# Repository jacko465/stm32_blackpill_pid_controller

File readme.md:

# STM32 Black Pill PID Motor Controller

*v1 deployment of the PID controller. With Pololu 4035 driver modules*

A PID-based motor control system for the STM32F411 Black Pill microcontroller, designed to control 4 DC motors with encoders via H-bridge drivers (e.g., TI DRV8874).

## Features

- **High-frequency PID control**: 1 kHz PID loop running on TIM10 interrupt
- **Encoder feedback**: 100 Hz encoder updates (quadrature decoding)
- **4 independent motor channels**: Each with PWM speed control and direction control
- **Configurable PID gains**: Kp, Ki, Kd parameters per motor
- **Anti-windup protection**: Integral clamping to prevent windup

## Hardware Configuration

### Motor Specifications
- Encoder: 11 PPR (basic) × 4 (quadrature) × 35.5 (gear ratio) = **1562 counts/revolution**
- PWM Frequency: Configured via TIM1 = 20kHz
- Control Loop: 1 ms update period (1 kHz)
- Encoder Reading: 10 ms update period (100 Hz)

### System Clock
- **84 MHz SYSCLK** derived from 25 MHz HSE crystal
- Configured with PLL (PLLM=25, PLLN=336, PLLP=4)

## Pinout

| Function | Pin | Timer/Channel |
|----------|-----|---------------|
| **Motor 1 PWM** | PA8 | TIM1 CH1 |
| **Motor 2 PWM** | PA9 | TIM1 CH2 |
| **Motor 3 PWM** | PA10 | TIM1 CH3 |
| **Motor 4 PWM** | PA11 | TIM1 CH4 |
| **Motor 1 DIR** | PB0 | GPIO |
| **Motor 2 DIR** | PB1 | GPIO |
| **Motor 3 DIR** | PB2 | GPIO |
| **Motor 4 DIR** | PB10 | GPIO |
| **Motor 1 Encoder A** | PA0 | TIM5 CH1 |
| **Motor 1 Encoder B** | PA1 | TIM5 CH2 |
| **Motor 2 Encoder A** | PA6 | TIM3 CH1 |
| **Motor 2 Encoder B** | PA7 | TIM3 CH2 |
| **Motor 3 Encoder A** | PB6 | TIM4 CH1 |
| **Motor 3 Encoder B** | PB7 | TIM4 CH2 |
| **Motor 4 Encoder A** | PA5 | TIM2 CH1 |
| **Motor 4 Encoder B** | PB3 | TIM2 CH2 |
| **USART2 TX** | PA2 | USART2 |
| **USART2 RX** | PA3 | USART2 |
| **LED** | PC13 | GPIO (onboard) |

## PID Configuration

Default PID gains (defined in [`motor.h`](include/motor.h)):
- **Kp**: 0.1
- **Ki**: 0.125
- **Kd**: 0.0
- **Integral Limit**: 5.0 (anti-windup)
- **Output Range**: -1.0 to 1.0 (bidirectional control)

## Motor Control Functions

This project has been coded for EN/PH driver control mode

The [`motor.c`](src/motor.c) module provides:
- `Motor_SetTargetRPM()`: Set target velocity in RPM
- `Motor_Forward()`: Drive motor forward with duty cycle
- `Motor_Reverse()`: Drive motor in reverse with duty cycle
- `Motor_Break()`: Active braking (both H-bridge outputs high)
- `Motor_Coast()`: Free-running coast (both outputs low)

## Building

This project uses **PlatformIO**. To build and upload

## Error Handling

The [`Error_Handler()`](src/main.c) function provides visual feedback via fast blinking of the onboard LED (PC13) if system initialization fails.

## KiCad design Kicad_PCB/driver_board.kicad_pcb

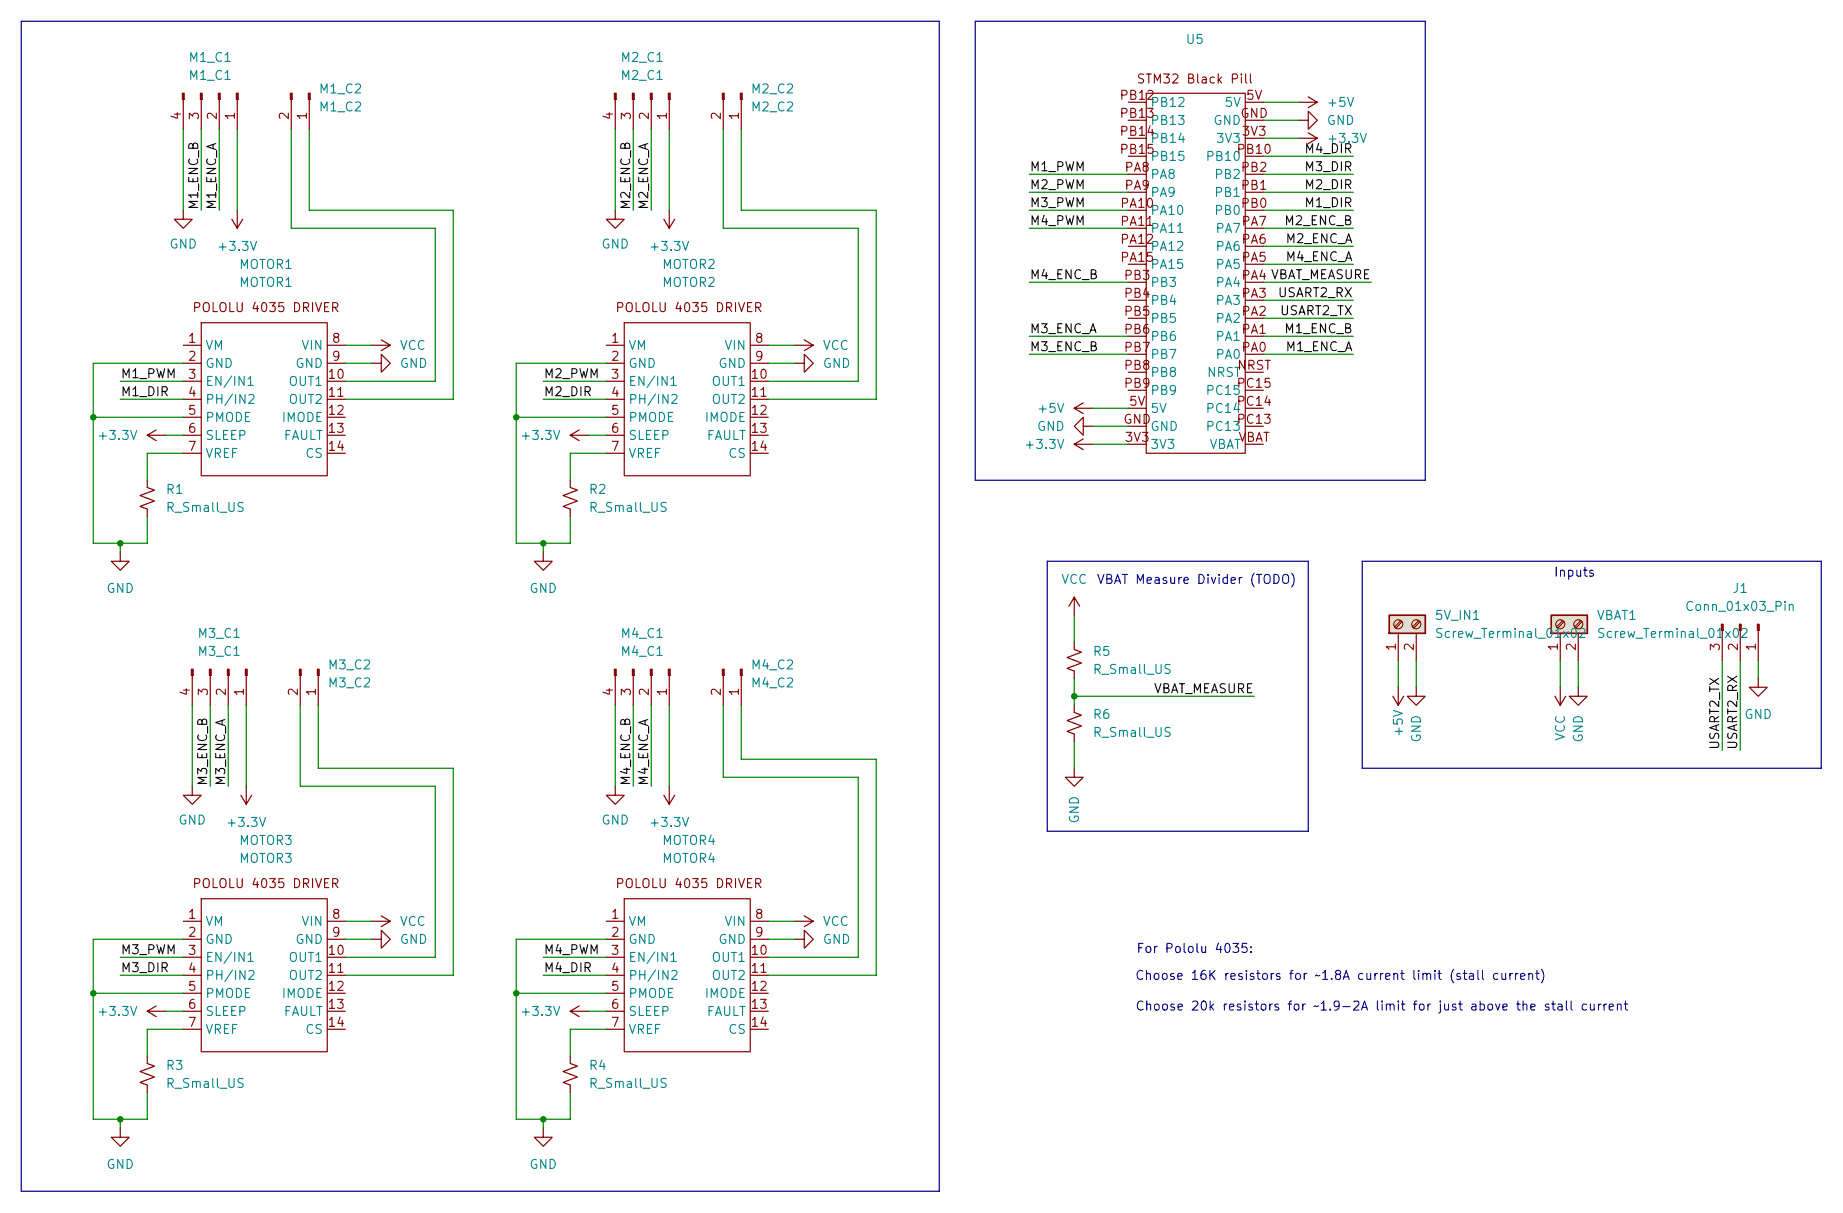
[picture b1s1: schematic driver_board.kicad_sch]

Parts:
5V_IN1: Screw_Terminal_01x02; TerminalBlock_MaiXu_MX126-5.0-02P_1x02_P5.00mm
J1: Conn_01x03_Pin; PinHeader_1x03_P2.54mm_Vertical
M1_C1: M1_C1; PinHeader_1x04_P2.54mm_Vertical
M1_C2: M1_C2; PinHeader_1x02_P2.54mm_Vertical
M2_C1: M2_C1; PinHeader_1x04_P2.54mm_Vertical
M2_C2: M2_C2; PinHeader_1x02_P2.54mm_Vertical
M3_C1: M3_C1; PinHeader_1x04_P2.54mm_Vertical
M3_C2: M3_C2; PinHeader_1x02_P2.54mm_Vertical
M4_C1: M4_C1; PinHeader_1x04_P2.54mm_Vertical
M4_C2: M4_C2; PinHeader_1x02_P2.54mm_Vertical
MOTOR1: MOTOR1; Pololu_4035_DRV8874_Motor_Driver
MOTOR2: MOTOR2; Pololu_4035_DRV8874_Motor_Driver
MOTOR3: MOTOR3; Pololu_4035_DRV8874_Motor_Driver
MOTOR4: MOTOR4; Pololu_4035_DRV8874_Motor_Driver
R1, R2, R3, R4, R5, R6: R_Small_US; R_Axial_DIN0309_L9.0mm_D3.2mm_P12.70mm_Horizontal
U5: STM32 Black Pill
VBAT1: Screw_Terminal_01x02; TerminalBlock_MaiXu_MX126-5.0-02P_1x02_P5.00mm

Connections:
+3.3V: M1_C1.1, M2_C1.1, M3_C1.1, M4_C1.1, MOTOR1.6 (SLEEP), MOTOR2.6 (SLEEP), MOTOR3.6 (SLEEP), MOTOR4.6 (SLEEP), U5.3V3
+5V: 5V_IN1.1, U5.5V
/M1_DIR: MOTOR1.4 (PH/IN2), U5.PB0
/M1_ENC_A: M1_C1.2, U5.PA0
/M1_ENC_B: M1_C1.3, U5.PA1
/M1_PWM: MOTOR1.3 (EN/IN1), U5.PA8
/M2_DIR: MOTOR2.4 (PH/IN2), U5.PB1
/M2_ENC_A: M2_C1.2, U5.PA6
/M2_ENC_B: M2_C1.3, U5.PA7
/M2_PWM: MOTOR2.3 (EN/IN1), U5.PA9
/M3_DIR: MOTOR3.4 (PH/IN2), U5.PB2
/M3_ENC_A: M3_C1.2, U5.PB6
/M3_ENC_B: M3_C1.3, U5.PB7
/M3_PWM: MOTOR3.3 (EN/IN1), U5.PA10
/M4_DIR: MOTOR4.4 (PH/IN2), U5.PB10
/M4_ENC_A: M4_C1.2, U5.PA5
/M4_ENC_B: M4_C1.3, U5.PB3
/M4_PWM: MOTOR4.3 (EN/IN1), U5.PA11
/USART2_RX: J1.2, U5.PA3
/USART2_TX: J1.3, U5.PA2
/VBAT_MEASURE: R5.2, R6.1, U5.PA4
GND: 5V_IN1.2, J1.1, M1_C1.4, M2_C1.4, M3_C1.4, M4_C1.4, MOTOR1.2 (GND), MOTOR1.5 (PMODE), MOTOR1.9 (GND), MOTOR2.2 (GND), MOTOR2.5 (PMODE), MOTOR2.9 (GND), MOTOR3.2 (GND), MOTOR3.5 (PMODE), MOTOR3.9 (GND), MOTOR4.2 (GND), MOTOR4.5 (PMODE), MOTOR4.9 (GND), R1.2, R2.2, R3.2, R4.2, R6.2, U5.GND, VBAT1.2
unnamed: M1_C2.1, MOTOR1.11 (OUT2)
unnamed: M1_C2.2, MOTOR1.10 (OUT1)
unnamed: M2_C2.1, MOTOR2.11 (OUT2)
unnamed: M2_C2.2, MOTOR2.10 (OUT1)
unnamed: M3_C2.1, MOTOR3.11 (OUT2)
unnamed: M3_C2.2, MOTOR3.10 (OUT1)
unnamed: M4_C2.1, MOTOR4.11 (OUT2)
unnamed: M4_C2.2, MOTOR4.10 (OUT1)
unnamed: MOTOR1.7 (VREF), R1.1
unnamed: MOTOR2.7 (VREF), R2.1
unnamed: MOTOR3.7 (VREF), R3.1
unnamed: MOTOR4.7 (VREF), R4.1
VCC: MOTOR1.8 (VIN), MOTOR2.8 (VIN), MOTOR3.8 (VIN), MOTOR4.8 (VIN), R5.1, VBAT1.1

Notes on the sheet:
VBAT Measure Divider (TODO)
Choose 20k resistors for ~1.9-2A limit for just above the stall current
Inputs
Choose 16K resistors for ~1.8A current limit (stall current)
For Pololu 4035:

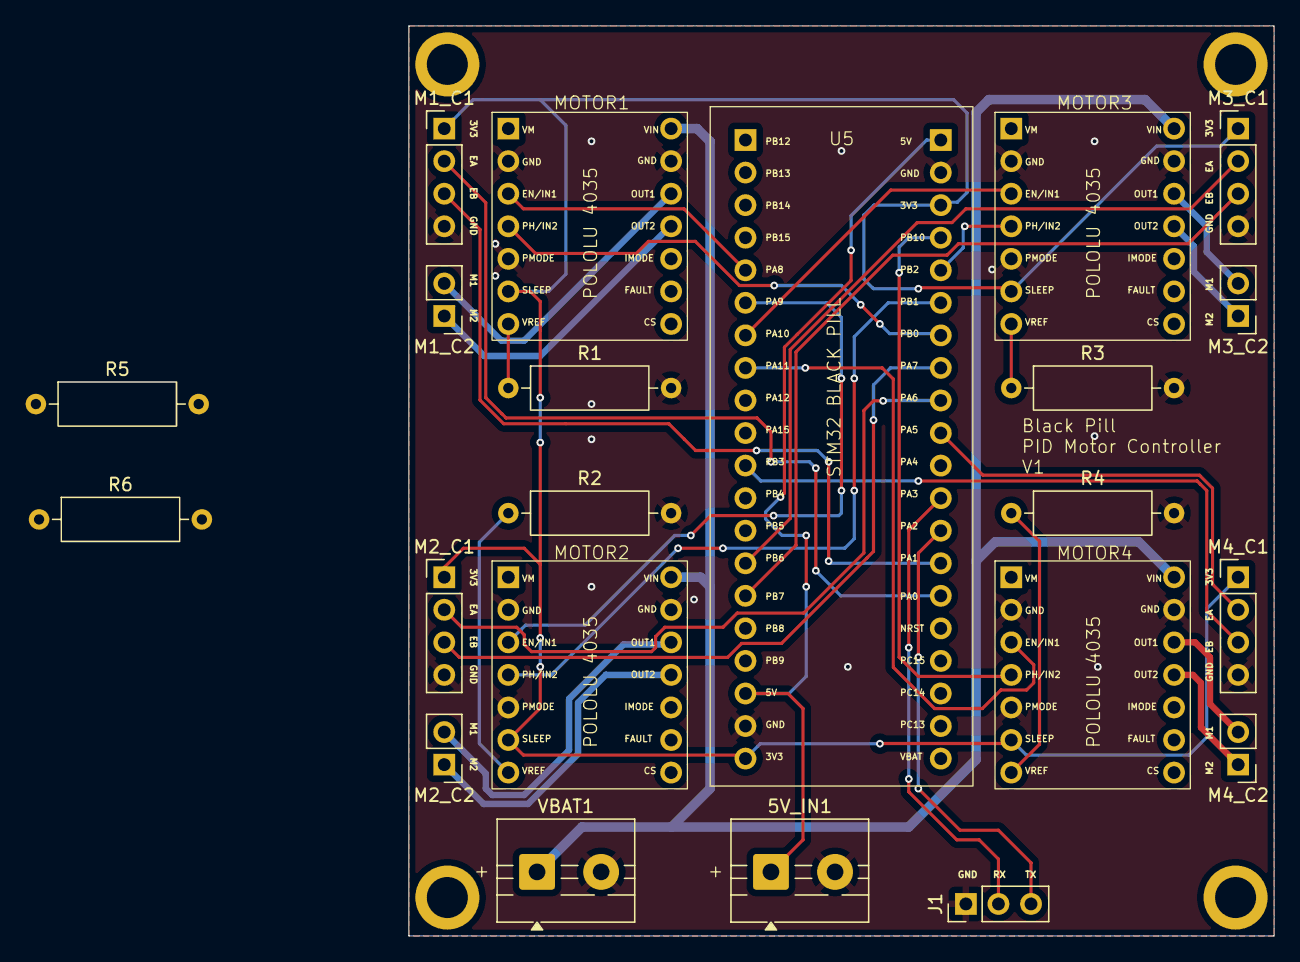
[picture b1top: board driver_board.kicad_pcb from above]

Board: 2 copper layers, 67.5 x 71.0 mm, 22 parts (0 on the bottom side), 35 nets.

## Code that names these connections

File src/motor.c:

#include "motor.h"

uint8_t Motors_Enabled = 0;
uint8_t ESTOP = 0;

// motor instances
Motor_t motor1 = {
    // Encoder state
    .prev_count = 0,
    .curr_count = 0,
    .rpm = 0.0f,
    .delta = 0,

    // Encoder timer pointer
    .htim_encoder = &htim5, // TIM5 (PA0/PA1) Motor 1 encoder

    //PID gains
    .kp = KP,
    .ki = KI,
    .kd = KD,

    // PID state
    .integral = 0.0f,
    .prev_error = 0.0f,
    .output = 0.0f,

    // Target
    .enabled = 0,
    .target_rpm = 0,
    .target_delta = 0,

    // Integral limit (anti-windup) 5x output clamp
    .integral_limit = PID_INTEGRAL_LIMIT,

    // Output limits
    .output_min = PID_OUTPUT_MIN,
    .output_max = PID_OUTPUT_MAX,

    // PWM output
    .htim_pwm = &htim1,                     // TIM1
    .pwm_channel = TIM_CHANNEL_1,           // PA8

    // DIR pin
    .dir_port = GPIOB,                      // PB0
    .dir_pin = GPIO_PIN_0                   // PB0
};

Motor_t motor2 = {
    // Encoder state
    .prev_count = 0,
    .curr_count = 0,
    .rpm = 0.0f,
    .delta = 0,

    // Encoder timer pointer
    .htim_encoder = &htim3, // TIM3 (PA6/PA7) Motor 2 encoder

    //PID gains
    .kp = KP,
    .ki = KI,
    .kd = KD,

    // PID state
    .integral = 0.0f,
    .prev_error = 0.0f,
    .output = 0.0f,

    // Target
    .enabled = 0,
    .target_rpm = 0,
    .target_delta = 0,

    // Integral limit (anti-windup) 5x output clamp
    .integral_limit = PID_INTEGRAL_LIMIT,

    // Output limits
    .output_min = PID_OUTPUT_MIN,
    .output_max = PID_OUTPUT_MAX,
    // PWM output
    .htim_pwm = &htim1,                     // TIM1
    .pwm_channel = TIM_CHANNEL_2,           // PA9

    // DIR pin
    .dir_port = GPIOB,                      // PB0
    .dir_pin = GPIO_PIN_1                   // PB1
};

Motor_t motor3 = {
    // Encoder state
    .prev_count = 0,
    .curr_count = 0,
    .rpm = 0.0f,
    .delta = 0,

    // Encoder timer pointer
    .htim_encoder = &htim4, // TIM4 (PB6/PB7) Motor 3 encoder

    //PID gains
    .kp = KP,
    .ki = KI,
    .kd = KD,

    // PID state
    .integral = 0.0f,
    .prev_error = 0.0f,
    .output = 0.0f,

    // Target
    .enabled = 0,
    .target_rpm = 0,
    .target_delta = 0,

    // Integral limit (anti-windup) 5x output clamp
    .integral_limit = PID_INTEGRAL_LIMIT,

    // Output limits
    .output_min = PID_OUTPUT_MIN,
    .output_max = PID_OUTPUT_MAX,
    // PWM output
    .htim_pwm = &htim1,                     // TIM1
    .pwm_channel = TIM_CHANNEL_3,           // PA10

    // DIR pin
    .dir_port = GPIOB,                      // PB0
    .dir_pin = GPIO_PIN_2                   // PB2
};

Motor_t motor4 = {
    // Encoder state
    .prev_count = 0,
    .curr_count = 0,
    .rpm = 0.0f,
    .delta = 0,

    // Encoder timer pointer
    .htim_encoder = &htim2, // TIM2 (PA0/PA1) Motor 4 encoder

    //PID gains
    .kp = KP,
    .ki = KI,
    .kd = KD,

    // PID state
    .integral = 0.0f,
    .prev_error = 0.0f,
    .output = 0.0f,

    // Target
    .enabled = 0,
    .target_rpm = 0,
    .target_delta = 0,

    // Integral limit (anti-windup) 5x output clamp
    .integral_limit = PID_INTEGRAL_LIMIT,

    // Output limits
    .output_min = PID_OUTPUT_MIN,
    .output_max = PID_OUTPUT_MAX,
    // PWM output
    .htim_pwm = &htim1,                     // TIM1
    .pwm_channel = TIM_CHANNEL_4,           // PA11

    // DIR pin
    .dir_port = GPIOB,                      // PB0
    .dir_pin = GPIO_PIN_10                  // PB10
};

// PID Loop function
void PID_UpdateMotor(Motor_t *motor)
{
    if (!motor->enabled)
    {
        Motor_Break(motor);
        return;
    }

    // Compute error terms
    // float error = (float)motor->target_delta - (float)(motor->delta);
    float error = motor->target_delta - (float)(motor->delta);
    motor->integral += error * PID_UPDATE_PERIOD;
    float derivative = (error - motor->prev_error) / PID_UPDATE_PERIOD;
    motor->prev_error = error;

    // Clamp integral to prevent windup
    if (motor->integral > motor->integral_limit) motor->integral = motor->integral_limit;
    if (motor->integral < -motor->integral_limit) motor->integral = -motor->integral_limit;

    // Compute PID
    motor->output = (motor->kp * error) + (motor->ki * motor->integral) + (motor->kd * derivative);

    // Clamp output
    if (motor->output > motor->output_max) motor->output = motor->output_max;
    if (motor->output < motor->output_min) motor->output = motor->output_min;

    // Apply output to motor
    Motor_ApplyOutput(motor);
}

// Update motor velocity (call every ~10ms)
void Update_Motor_RPM(Motor_t *motor)
{
    motor->prev_count = motor->curr_count;
    motor->curr_count = Encoder_GetCount(motor->htim_encoder);
    motor->delta = (int16_t)(motor->curr_count - motor->prev_count);
    float counts_per_sec = motor->delta * ENCODER_UPDATE_FREQUENCY_HZ;
    motor->rpm = counts_per_sec * 60.0f / ENCODER_COUNTS_PER_REV;
}

// Set motor RPM target
void Motor_SetTargetRPM(Motor_t *motor, int32_t target_rpm)
{
    motor->target_rpm = target_rpm;
    motor->target_delta = target_rpm * ((float)ENCODER_COUNTS_PER_REV / 60.0f) * ENCODER_UPDATE_PERIOD;
}

void Enable_Motors(void)
{
    Motors_Enabled = 1;
    motor1.enabled = 1;
    motor2.enabled = 1;
    motor3.enabled = 1;
    motor4.enabled = 1;
}

void Disable_Motors(void)
{
    Motors_Enabled = 0;
    motor1.enabled = 0;
    motor2.enabled = 0;
    motor3.enabled = 0;
    motor4.enabled = 0;
}

void SET_ESTOP(void)
{
    ESTOP = 1;
    Set_Left_RPM(0);
    Set_Right_RPM(0);
    Disable_Motors();
}

// motor driving methods

// Motor apply output (set by PID)
void Motor_ApplyOutput(Motor_t *motor)
{
    float duty_cycle = motor->output;
    if (duty_cycle > 0.0f)
    {
        Motor_Forward(motor, duty_cycle);
    }
    else if (duty_cycle < 0.0f)
    {
        Motor_Reverse(motor, -duty_cycle);
    }
    else
    {
        Motor_Break(motor);
    }
}

// Motor break function
void Motor_Break(Motor_t *motor)
{
    SET_PWM_DC(motor->htim_pwm, motor->pwm_channel, 0.0f);
    HAL_GPIO_WritePin(motor->dir_port, motor->dir_pin, GPIO_PIN_SET);
}

// Motor coast function (pololu 4035 does not support coasting in ph/en mode)
// void Motor_Coast(Motor_t *motor)
// {
//     SET_PWM_DC(motor->htim_pwm, motor->pwm_channel, 0.0f);
//     HAL_GPIO_WritePin(motor->dir_port, motor->dir_pin, GPIO_PIN_RESET);
// }

// Basic motor forward function
void Motor_Forward(Motor_t *motor, float duty_cycle)
{
    SET_PWM_DC(motor->htim_pwm, motor->pwm_channel, duty_cycle);
    HAL_GPIO_WritePin(motor->dir_port, motor->dir_pin, GPIO_PIN_RESET);
}

// Basic motor reverse function
void Motor_Reverse(Motor_t *motor, float duty_cycle)
{
    SET_PWM_DC(motor->htim_pwm, motor->pwm_channel, duty_cycle);
    HAL_GPIO_WritePin(motor->dir_port, motor->dir_pin, GPIO_PIN_SET);
}

// Skid steer functions
void Set_Left_RPM(int32_t rpm)
{
    Motor_SetTargetRPM(&motor1, rpm);
    Motor_SetTargetRPM(&motor2, rpm);
}

void Set_Right_RPM(int32_t rpm)
{
    Motor_SetTargetRPM(&motor3, rpm);
    Motor_SetTargetRPM(&motor4, rpm);
}

void Spin_Left(int32_t rpm)
{
    Motor_SetTargetRPM(&motor1, -rpm);
    Motor_SetTargetRPM(&motor2, -rpm);
    Motor_SetTargetRPM(&motor3, rpm);
    Motor_SetTargetRPM(&motor4, rpm);
}

void Spin_Right(int32_t rpm)
{
    Motor_SetTargetRPM(&motor1, rpm);
    Motor_SetTargetRPM(&motor2, rpm);
    Motor_SetTargetRPM(&motor3, -rpm);
    Motor_SetTargetRPM(&motor4, -rpm);
}

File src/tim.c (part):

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		__HAL_RCC_GPIOA_CLK_ENABLE();
		__HAL_RCC_GPIOB_CLK_ENABLE();
		/**TIM2 GPIO Configuration
		PA5     ------> TIM2_CH1
		PB3     ------> TIM2_CH2
		*/
		GPIO_InitStruct.Pin = GPIO_PIN_5;
		GPIO_InitStruct.Mode = GPIO_MODE_AF_PP;
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
		__HAL_RCC_GPIOA_CLK_ENABLE();
		/**TIM3 GPIO Configuration
		PA6     ------> TIM3_CH1
		PA7     ------> TIM3_CH2
		*/
		GPIO_InitStruct.Pin = GPIO_PIN_6|GPIO_PIN_7;
		GPIO_InitStruct.Mode = GPIO_MODE_AF_PP;
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
		__HAL_RCC_GPIOB_CLK_ENABLE();
		/**TIM4 GPIO Configuration
		PB6     ------> TIM4_CH1
		PB7     ------> TIM4_CH2
		*/
		GPIO_InitStruct.Pin = GPIO_PIN_6|GPIO_PIN_7;
		GPIO_InitStruct.Mode = GPIO_MODE_AF_PP;
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
		__HAL_RCC_GPIOA_CLK_ENABLE();
		/**TIM5 GPIO Configuration
		PA0-WKUP     ------> TIM5_CH1
		PA1     ------> TIM5_CH2
		*/
		GPIO_InitStruct.Pin = GPIO_PIN_0|GPIO_PIN_1;
		GPIO_InitStruct.Mode = GPIO_MODE_AF_PP;
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
		__HAL_RCC_GPIOA_CLK_ENABLE();
		/**TIM1 GPIO Configuration
		PA8     ------> TIM1_CH1
		PA9     ------> TIM1_CH2
		PA10     ------> TIM1_CH3
		PA11     ------> TIM1_CH4
		*/
		GPIO_InitStruct.Pin = GPIO_PIN_8|GPIO_PIN_9|GPIO_PIN_10|GPIO_PIN_11;
		GPIO_InitStruct.Mode = GPIO_MODE_AF_PP;
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		__HAL_RCC_TIM2_CLK_DISABLE();

		/**TIM2 GPIO Configuration
		PA5     ------> TIM2_CH1
		PB3     ------> TIM2_CH2
		*/
		HAL_GPIO_DeInit(GPIOA, GPIO_PIN_5);

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		__HAL_RCC_TIM3_CLK_DISABLE();

		/**TIM3 GPIO Configuration
		PA6     ------> TIM3_CH1
		PA7     ------> TIM3_CH2
		*/
		HAL_GPIO_DeInit(GPIOA, GPIO_PIN_6|GPIO_PIN_7);

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		__HAL_RCC_TIM4_CLK_DISABLE();

		/**TIM4 GPIO Configuration
		PB6     ------> TIM4_CH1
		PB7     ------> TIM4_CH2
		*/
		HAL_GPIO_DeInit(GPIOB, GPIO_PIN_6|GPIO_PIN_7);

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		__HAL_RCC_TIM5_CLK_DISABLE();

		/**TIM5 GPIO Configuration
		PA0-WKUP     ------> TIM5_CH1
		PA1     ------> TIM5_CH2
		*/
		HAL_GPIO_DeInit(GPIOA, GPIO_PIN_0|GPIO_PIN_1);

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
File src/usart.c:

#include "usart.h"

UART_HandleTypeDef huart2;
DMA_HandleTypeDef hdma_usart2_rx;

void MX_USART2_UART_Init(void)
{

	// Init USART2
	huart2.Instance = USART2;
	huart2.Init.BaudRate = 115200;
	huart2.Init.WordLength = UART_WORDLENGTH_8B;
	huart2.Init.StopBits = UART_STOPBITS_1;
	huart2.Init.Parity = UART_PARITY_NONE;
	huart2.Init.Mode = UART_MODE_TX_RX;
	huart2.Init.HwFlowCtl = UART_HWCONTROL_NONE;
	huart2.Init.OverSampling = UART_OVERSAMPLING_16;
	if (HAL_UART_Init(&huart2) != HAL_OK)
	{
		Error_Handler();
	}
}

void HAL_UART_MspInit(UART_HandleTypeDef* uartHandle)
{

	GPIO_InitTypeDef GPIO_InitStruct = {0};
	if(uartHandle->Instance==USART2)
	{
		/* USART2 clock enable */
		__HAL_RCC_USART2_CLK_ENABLE();

		__HAL_RCC_GPIOA_CLK_ENABLE();
		/**USART2 GPIO Configuration
		PA2     ------> USART2_TX
		PA3     ------> USART2_RX
		*/
		GPIO_InitStruct.Pin = GPIO_PIN_2|GPIO_PIN_3;
		GPIO_InitStruct.Mode = GPIO_MODE_AF_PP;
		GPIO_InitStruct.Pull = GPIO_NOPULL;
		GPIO_InitStruct.Speed = GPIO_SPEED_FREQ_VERY_HIGH;
		GPIO_InitStruct.Alternate = GPIO_AF7_USART2;
		HAL_GPIO_Init(GPIOA, &GPIO_InitStruct);

		/* USART2 DMA Init */
		/* USART2_RX Init */
		hdma_usart2_rx.Instance = DMA1_Stream5;
		hdma_usart2_rx.Init.Channel = DMA_CHANNEL_4;
		hdma_usart2_rx.Init.Direction = DMA_PERIPH_TO_MEMORY;
		hdma_usart2_rx.Init.PeriphInc = DMA_PINC_DISABLE;
		hdma_usart2_rx.Init.MemInc = DMA_MINC_ENABLE;
		hdma_usart2_rx.Init.PeriphDataAlignment = DMA_PDATAALIGN_BYTE;
		hdma_usart2_rx.Init.MemDataAlignment = DMA_MDATAALIGN_BYTE;
		hdma_usart2_rx.Init.Mode = DMA_CIRCULAR;
		hdma_usart2_rx.Init.Priority = DMA_PRIORITY_LOW;
		hdma_usart2_rx.Init.FIFOMode = DMA_FIFOMODE_DISABLE;
		if (HAL_DMA_Init(&hdma_usart2_rx) != HAL_OK)
		{
			Error_Handler();
		}

		__HAL_LINKDMA(uartHandle,hdmarx,hdma_usart2_rx);

		/* USART2 interrupt Init */
		HAL_NVIC_SetPriority(USART2_IRQn, 0, 0);
		HAL_NVIC_EnableIRQ(USART2_IRQn);
	}
}

void HAL_UART_MspDeInit(UART_HandleTypeDef* uartHandle)
{

	if(uartHandle->Instance==USART2)
	{
		/* Peripheral clock disable */
		__HAL_RCC_USART2_CLK_DISABLE();

		/**USART2 GPIO Configuration
		PA2     ------> USART2_TX
		PA3     ------> USART2_RX
		*/
		HAL_GPIO_DeInit(GPIOA, GPIO_PIN_2|GPIO_PIN_3);

		/* USART2 DMA DeInit */
		HAL_DMA_DeInit(uartHandle->hdmarx);

		/* USART2 interrupt Deinit */
		HAL_NVIC_DisableIRQ(USART2_IRQn);
	}
}

// Redirect printf to USART2
int _write(int file, char *data, int len)
{
		HAL_UART_Transmit(&huart2, (uint8_t*)data, len, HAL_MAX_DELAY);
		return len;
}

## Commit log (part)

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2025-12-14 initial commit, scaffolding complete
2025-12-14 code ported from stm32 blue pill controller, not fully implemented yet. Sanity check blink running on ISR working.
2025-12-14 changed a motor dir pin, added readme
2025-12-16 set new motor and encoder params, enabled hardware float on mcu
2025-12-16 created other motor variables and enabled them in main
2025-12-16 changed some variable declarations inside Motor_t to be volatile
2025-12-17 created default pid output limits and anti windup integral limit definitions
2025-12-17 added usart dma scaffolding
2025-12-17 more usart2 rx dma and idle isr scaffolding
2026-01-01 base code working for the stm32 black pill and pololu 4035 drivers
2026-01-03 PID tuned and parameters set for PID on target delta (for slam bot testing)
2026-01-05 got USART RX working with simple echo
2026-01-05 Implemented basic telemetry
2026-01-05 added motor enable/disable and skid steer methods
2026-01-05 removed buildlog
2026-01-06 fixed bug where motor4 negative values broke it
2026-01-06 added serial message parsing and SET command implementation
2026-01-06 basic comms completed
2026-01-06 added ping
2026-01-06 changed some comms to make things more reliable finished basic motor testing via comms
2026-01-10 changed serial port in motor test
2026-01-10 changed ACK serial strings
2026-04-28 added configured pwm frequency in readme
